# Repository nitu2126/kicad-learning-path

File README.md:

# KiCad Learning Path

> My hands-on journey from complete beginner to advanced electronics and PCB design with KiCad, built from small, simple circuits.
> Every project teaches one new idea and is documented with schematics, calculations, timing diagrams, layout rules, verification reports and manufacturing files.

## Table of contents

- [About this repository](#about-this-repository)
- [Learning approach](#learning-approach)
- [Projects so far](#projects-so-far)
- [Roadmap](#roadmap)
- [Coverage by track](#coverage-by-track)
- [Components index](#components-index)
- [What every project includes](#what-every-project-includes)
- [Repository structure](#repository-structure)
- [Tools](#tools)
- [How to open a project](#how-to-open-a-project)
- [Feedback](#feedback)
- [License](#license)

## About this repository

This repository documents my path through electronics and PCB design. I build one small circuit at a time, calculate it by hand, design it in KiCad, check it with ERC and DRC, prepare the manufacturing files, and write down what I learned.

The projects are ordered so that each one builds on the last. If you are learning too, start at Project 1 and work forward. The complete plan, with the components and ideas of every project, is in [ROADMAP.md](ROADMAP.md).

## Learning approach

| Rule | Why |
|---|---|
| One new idea per board | So you can see exactly what each component does |
| About 12 parts or fewer | Small enough to understand every connection |
| Through-hole parts and 0805 SMD only | Hand-solderable, no special equipment |
| 2-layer board, standard KiCad libraries | Cheap to build and easy to reproduce |
| Calculate first, then build, then measure | Theory is checked against reality |
| Timing or waveform diagram wherever signals change over time | Turns formulas into something you can verify on an oscilloscope |

## Projects so far

| # | Project | Preview | What it teaches | Documentation |
|---|---|---|---|---|
| 1 | [LED + Push-Button](01-led-button/) |  | Ohm's law, LED current limiting, resistors and switches, the full KiCad workflow, Gerber export | [README](01-led-button/README.md) · [Design notes](01-led-button/docs/DESIGN_NOTES.md) |
| 2 | [555 LED Blinker](02-555-blinker/) |  | Capacitors, RC time constant, the 555 timer, decoupling, ground pours and vias, timing diagram | [README](02-555-blinker/README.md) · [Design notes](02-555-blinker/docs/DESIGN_NOTES.md) |
| 3 | [Voltage Divider, Potentiometer and Light Sensor](03-voltage-divider/) |  | The voltage divider formula, the loading effect, potentiometer, LDR light sensor, test points, transfer curves | [README](03-voltage-divider/README.md) · [Design notes](03-voltage-divider/docs/DESIGN_NOTES.md) |
| 4 | [NPN Transistor Switch](04-npn-transistor-switch/) |  | The transistor as a switch, base resistor and saturation, flyback diode, net classes, switching waveform | [README](04-npn-transistor-switch/README.md) · [Design notes](04-npn-transistor-switch/docs/DESIGN_NOTES.md) |

## Roadmap

Fifteen simple circuits, from the first resistor to a complete microcontroller board.

| # | Project | Level | Track | Key ideas | Status |
|---|---|---|---|---|---|
| 1 | [LED + Push-Button](01-led-button/) | Beginner | Basics | Resistor, LED, switch, Ohm's law | Done |
| 2 | [555 LED Blinker](02-555-blinker/) | Beginner | Timing | Capacitor, timer IC, RC timing, decoupling | Done |
| 3 | [Voltage Divider, Potentiometer and Light Sensor](03-voltage-divider/) | Beginner | Analog | Divider formula, loading effect, LDR, test points | Done |
| 4 | [NPN Transistor Switch](04-npn-transistor-switch/) | Beginner | Analog and power | BJT, base resistor, flyback diode, saturation | In progress |
| 5 | Diode Power Entry and 5 V Linear Regulator | Beginner | Power | Reverse-polarity protection, regulator, heat dissipation | Planned |
| 6 | RC Low-Pass Filter | Intermediate | Analog | Cutoff frequency, step response, frequency response | Planned |
| 7 | Op-Amp Buffer and Amplifier | Intermediate | Analog | Feedback, gain, single-supply operation | Planned |
| 8 | Comparator Night-Light | Intermediate | Analog to digital | Comparator, hysteresis, sensor to switch | Planned |
| 9 | Logic Gates Trainer | Intermediate | Digital | 74HC gates, truth tables, logic levels, pull-downs | Planned |
| 10 | Switch Debouncer and D Flip-Flop | Intermediate | Digital | Contact bounce, SR latch, clocked memory | Planned |
| 11 | LED Chaser (555 + Decade Counter) | Advanced | Digital | Counters, clocking, sequential logic | Planned |
| 12 | MOSFET Load Switch and PWM Dimmer | Advanced | Power and analog | N-MOSFET, gate drive, PWM duty cycle | Planned |
| 13 | Buck Converter | Advanced | Power | Inductor, switching regulator, efficiency, loop layout | Planned |
| 14 | Digital Counter with 7-Segment Display | Advanced | Digital | Counter and decoder IC, display driving | Planned |
| 15 | Microcontroller Starter Board (ATtiny) | Advanced | Digital, analog and power | MCU, programming header, reset, ADC input | Planned |

**Status:** Done = built, verified and documented. In progress = designed or being documented. Planned = not started. The plan may be adjusted as I learn.

## Coverage by track

| Track | Projects |
|---|---|
| Analog | 3, 4, 6, 7, 8, 12, 15 |
| Digital | 2, 9, 10, 11, 14, 15 |
| Power | 4, 5, 12, 13, 15 |

## Components index

| Component | First used in |
|---|---|
| Resistor, LED, push-button | Project 1 |
| Capacitor (ceramic and electrolytic), 555 timer | Project 2 |
| Potentiometer, light-dependent resistor | Project 3 |
| NPN transistor | Project 4 |
| Diode, linear voltage regulator | Project 5 |
| Op-amp | Project 7 |
| Comparator | Project 8 |
| Logic gates | Project 9 |
| Flip-flop | Project 10 |
| Counter | Project 11 |
| MOSFET | Project 12 |
| Inductor, switching regulator | Project 13 |
| Decoder and 7-segment display | Project 14 |
| Microcontroller | Project 15 |

## What every project includes

- **README**: overview, specifications, images, bill of materials, netlist, testing and status
- **Design notes**: electronics theory, step-by-step calculations with worst-case analysis, KiCad configuration, layout rules and the reasons for them
- **Timing or waveform diagram** wherever signals change over time
- **Verification**: saved ERC and DRC reports and a Gerber viewer check
- **Manufacturing files**: Gerbers, drill files and BOM, ready for a low-cost fab
- **Test procedure**: expected measurements to compare against the real board

## Repository structure

```
kicad-learning-path/
├── README.md                    this index
├── ROADMAP.md                   the full 15-project plan
├── LICENSE
├── .gitignore
├── 01-led-button/
│   ├── README.md
│   ├── 01_led_button.kicad_pro / .kicad_sch / .kicad_pcb
│   ├── fabrication/             Gerbers, drill files, BOM
│   └── docs/                    design notes, schematic PDF, images, reports
├── 02-555-blinker/
│   ├── README.md
│   ├── 02_555_blinker.kicad_pro / .kicad_sch / .kicad_pcb
│   ├── fabrication/             Gerbers, drill files, BOM
│   └── docs/                    design notes, schematic PDF, timing diagram, images, reports
├── 03-voltage-divider/
│   ├── README.md
│   ├── 03_voltage_divider.kicad_pro / .kicad_sch / .kicad_pcb
│   ├── fabrication/             Gerbers, drill files, BOM
│   └── docs/                    design notes, schematic PDF, transfer curves, response diagram, images, reports
├── 04-npn-transistor-switch/
│   ├── README.md
│   ├── 04_npn_transistor_switch.kicad_pro / .kicad_sch / .kicad_pcb
│   ├── fabrication/             Gerbers, drill files, BOM
│   └── docs/                    design notes, schematic PDF, switching waveform, saturation curve, images, reports
└── 05-... to 15-...             added as each project is completed
```

**Naming:** project folders are `NN-short-name/` and the KiCad files inside are `NN_short_name.*`.

**Every project folder follows the same layout:**

```
NN-short-name/
├── README.md
├── NN_short_name.kicad_pro / .kicad_sch / .kicad_pcb
├── fabrication/
│   ├── gerbers/
│   ├── NN_short_name_gerbers.zip
│   └── bom.csv
└── docs/
    ├── DESIGN_NOTES.md
    ├── schematic.pdf
    ├── images/
    └── reports/
```

## Tools

| Tool | Version |
|---|---|
| KiCad | 10.x |
| Libraries | Standard KiCad libraries only |
| Target fab | Low-cost 2-layer service (for example JLCPCB) |
| Gerber check | KiCad Gerber Viewer or any third-party viewer |
| Version control | Git and GitHub |

## How to open a project

1. Install [KiCad](https://www.kicad.org/download/).
2. Clone or download this repository.
3. Open the `.kicad_pro` file inside any project folder.

## Feedback

Spotted a mistake in a calculation, or have a suggestion for a better layout or a simpler explanation? Please open an issue. Corrections are welcome.

## License

Released under the [MIT License](LICENSE).

Author: **Nitish Ghadage** · [GitHub](https://github.com/nitu2126)

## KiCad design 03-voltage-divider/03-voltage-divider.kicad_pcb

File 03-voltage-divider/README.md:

# Voltage Divider, Potentiometer and Light Sensor

> Three analog voltage dividers on one 5 V board: a fixed divider with a switchable load, a potentiometer, and a light-dependent resistor. Five test points make every voltage easy to measure.
> **Project 3** of my [KiCad learning path](../README.md): the voltage divider formula, the loading effect, the potentiometer and the LDR.

## Table of contents

- [Overview](#overview)
- [Key specifications](#key-specifications)
- [Gallery](#gallery)
- [Transfer curves and response](#transfer-curves-and-response)
- [How the circuits work](#how-the-circuits-work)
- [Design calculations (summary)](#design-calculations-summary)
- [Purpose of each component](#purpose-of-each-component)
- [Bill of materials](#bill-of-materials)
- [Netlist](#netlist)
- [Repository structure](#repository-structure)
- [Getting started](#getting-started)
- [Testing](#testing)
- [Verification status](#verification-status)
- [Future improvements](#future-improvements)
- [License](#license)

## Overview

Projects 1 and 2 produced outputs you could see: an LED that lit and an LED that blinked. This board produces **voltages you measure** with a multimeter. It teaches the most useful circuit in electronics, the voltage divider, in three forms:

| Section | Circuit | What it demonstrates |
|---|---|---|
| A | Fixed divider `R1` / `R2`, with a load `R3` switched in by jumper `JP1` | The divider formula, and how a load pulls the output down (the loading effect) |
| B | Potentiometer `RV1` across the supply | A variable divider, and how the wiper position sets the output |
| C | Light-dependent resistor `LDR1` and `R4` | Turning a changing resistance into a changing voltage |

New ideas compared with Project 2:

1. The voltage divider formula and its Thevenin equivalent
2. The loading effect, and why measuring a circuit can change it
3. A three-terminal potentiometer
4. A sensor whose resistance depends on light (power-law behaviour)
5. Test points for measurement
6. A jumper to change the circuit without soldering
7. Silkscreen graphics to group sections on the board

The full engineering write-up (theory, derivations, KiCad configuration, layout rules, test procedure) is in [`docs/DESIGN_NOTES.md`](docs/DESIGN_NOTES.md).

## Key specifications

| Parameter | Value |
|---|---|
| Supply voltage | 5 V DC via `J1` |
| Section A output `VA` (`TP3`) | 2.50 V unloaded, 1.67 V with `JP1` fitted |
| Section B output `VB` (`TP4`) | 0 V to 5 V, set by `RV1` |
| Section C output `VC` (`TP5`) | about 0.05 V in the dark, about 2 V at 10 lux, about 3.6 V at 100 lux (typical) |
| Supply current | about 0.95 mA typical, 1.29 mA maximum |
| Board layers | 2 |
| Board thickness | 1.6 mm |
| Copper weight | 1 oz (35 µm) |
| Board size | 70 × 40 mm |
| Components | 13 (8 circuit parts and 5 test points) |
| Pads / nets | 22 / 6 |
| Design tool | KiCad 10.0.x |
| ERC / DRC | 0 errors / 0 errors |

## Gallery

### Schematic

Full-size PDF: [`docs/schematic.pdf`](docs/schematic.pdf)

### PCB layout

### 3D views

| Top | Bottom |
|---|---|
|  |  |

## Transfer curves and response

### Transfer curves

| Plot | What it shows |
|---|---|
| A. Fixed divider | The output falls as the load resistance falls. With a 10 kΩ load (`JP1` fitted) it drops from 2.50 V to 1.67 V |
| B. Potentiometer | A straight line from 0 V to 5 V when unloaded. A 10 kΩ load on the wiper bends the curve (2.0 V instead of 2.5 V at mid-travel) |
| C. LDR divider | Output rises with light on a log scale. The shaded band is the part-to-part spread of the LDR (10 kΩ to 20 kΩ at 10 lux) |

### LDR response in time

When the light changes, the LDR follows with a lag of tens of milliseconds (datasheet: about 20 ms rising, 30 ms falling), so `VC` rises and falls smoothly rather than instantly. After bright light the real part can take seconds to settle back to its dark value. This diagram is an illustrative first-order approximation.

## How the circuits work

```
 +5V ──┬──────────────┬──────────────────┬──────────────┐
       R1 10k         │                  LDR1           │
       │              RV1 10k            │               │
 VA ───┼── JP1 ─ R3   │◄── wiper = VB    VC ──┬── TP5    │
       │         10k  │                       R4 10k     │
       R2 10k         │                       │          │
 GND ──┴──────────────┴───────────────────────┴──────────┘
```

**A. Fixed divider.** `R1` and `R2` form a series loop, so the same current flows through both. The output between them is the share of the supply that falls across `R2`. Fitting a shunt on `JP1` connects `R3` in parallel with `R2`, which lowers the lower half of the divider and pulls `VA` down.

**B. Potentiometer.** The two ends of `RV1` connect to `+5V` and `GND`. The wiper touches the track at an adjustable point and picks off the voltage there, so turning the shaft sweeps `VB` smoothly from 0 V to 5 V.

**C. LDR divider.** In the light the LDR's resistance is low, so most of the supply falls across `R4` and `VC` is high. In the dark the LDR's resistance is very high, so most of the supply falls across the LDR and `VC` is low.

## Design calculations (summary)

**Voltage divider:**

$$V_{out} = V_{in} \times \frac{R_2}{R_1 + R_2} \qquad V_A = 5.0\ \text{V} \times \frac{10\ \text{k}\Omega}{10\ \text{k}\Omega + 10\ \text{k}\Omega} = 2.50\ \text{V}$$

**Loading effect** (a load $R_L$ in parallel with $R_2$):

$$V_{A,loaded} = V_{in} \times \frac{R_2 \parallel R_L}{R_1 + (R_2 \parallel R_L)} = 5.0\ \text{V} \times \frac{5\ \text{k}\Omega}{10\ \text{k}\Omega + 5\ \text{k}\Omega} = 1.67\ \text{V}$$

**Potentiometer** (wiper at fraction $x$ of the travel, unloaded):

$$V_B = V_{in} \times x$$

**LDR divider** (LDR on the supply side):

$$V_C = V_{in} \times \frac{R_4}{R_4 + R_{LDR}} \qquad R_{LDR}(E) = R_{10}\left(\frac{E}{10\ \text{lux}}\right)^{-\gamma}$$

| Illuminance | `R_LDR` (typical: 15 kΩ at 10 lux, γ = 0.6) | `VC` |
|---|---|---|
| Dark (0 lux) | 1 MΩ or more | 0.05 V or less |
| 1 lux | 59.7 kΩ | 0.72 V |
| 10 lux | 15.0 kΩ | 2.00 V |
| 100 lux | 3.77 kΩ | 3.63 V |
| 1000 lux | 0.95 kΩ | 4.57 V |

The full derivations, tolerance analysis, loading tables and power checks are in [`docs/DESIGN_NOTES.md`](docs/DESIGN_NOTES.md#3-calculations).

## Purpose of each component

| Ref | Value | Purpose |
|---|---|---|
| `J1` | 2-pin header | Brings in 5 V (pin 1) and ground (pin 2) |
| `R1` | 10 kΩ | Upper resistor of the fixed divider |
| `R2` | 10 kΩ | Lower resistor of the fixed divider. Equal to `R1`, so `VA` is exactly half the supply |
| `R3` | 10 kΩ | Load resistor that `JP1` connects across `R2`, to demonstrate the loading effect |
| `JP1` | 2-pin header and shunt | Fitted: load connected. Removed: no load |
| `RV1` | 10 kΩ linear potentiometer | Variable divider. 10 kΩ draws only 0.5 mA and keeps the wiper impedance low |
| `LDR1` | GL5528 | Light sensor: 10 kΩ to 20 kΩ at 10 lux, at least 1 MΩ in the dark |
| `R4` | 10 kΩ | Fixed half of the LDR divider. Close to the LDR's resistance at typical room light, which gives good sensitivity |
| `TP1` | Test point | Probe point for `+5V` |
| `TP2` | Test point | Probe point for `GND` (reference for all measurements) |
| `TP3` | Test point | Probe point for `VA` |
| `TP4` | Test point | Probe point for `VB` |
| `TP5` | Test point | Probe point for `VC` |

## Bill of materials

| Ref | Qty | Value | Footprint | Description |
|---|---|---|---|---|
| `J1` | 1 | Conn_01x02_Pin | `PinHeader_1x02_P2.54mm_Vertical` | 2-pin header, 5 V in |
| `R1` | 1 | 10 kΩ | `R_0805_2012Metric` | Resistor, 1 % |
| `R2` | 1 | 10 kΩ | `R_0805_2012Metric` | Resistor, 1 % |
| `R3` | 1 | 10 kΩ | `R_0805_2012Metric` | Resistor, 1 % |
| `R4` | 1 | 10 kΩ | `R_0805_2012Metric` | Resistor, 1 % |
| `JP1` | 1 | Jumper_2_Open | `PinHeader_1x02_P2.54mm_Vertical` | 2-pin header, plus one 2.54 mm shunt |
| `RV1` | 1 | 10 kΩ | `Potentiometer_Bourns_3296W_Vertical` | Linear trimmer potentiometer |
| `LDR1` | 1 | GL5528 | `R_LDR_5.1x4.3mm_P3.4mm_Vertical` | CdS photoresistor, 5 mm |
| `TP1` to `TP5` | 5 | TestPoint | `TestPoint_THTPad_D2.0mm_Drill1.0mm` | Through-hole test points |

The same list is available as CSV in [`fabrication/bom.csv`](fabrication/bom.csv).

## Netlist

| Net | Connections |
|---|---|
| `+5V` | `J1`-1, `R1`-1, `RV1`-3, `LDR1`-1, `TP1` |
| `GND` | `J1`-2, `R2`-2, `R3`-2, `RV1`-1, `R4`-2, `TP2` |
| `VA` | `R1`-2, `R2`-1, `JP1`-1, `TP3` |
| `LOAD` | `JP1`-2, `R3`-1 |
| `VB` | `RV1`-2 (wiper), `TP4` |
| `VC` | `LDR1`-2, `R4`-1, `TP5` |

## Repository structure

This project lives in the `03-voltage-divider/` folder of the [kicad-learning-path](../README.md) repository.

```
03-voltage-divider/
├── README.md
├── 03_voltage_divider.kicad_pro     KiCad project file
├── 03_voltage_divider.kicad_sch     Schematic
├── 03_voltage_divider.kicad_pcb     PCB layout
├── fabrication/
│   ├── gerbers/                     Gerber and drill files
│   ├── 03_voltage_divider_gerbers.zip
│   └── bom.csv
└── docs/
    ├── DESIGN_NOTES.md              Full engineering documentation
    ├── schematic.pdf
    ├── images/                      Transfer curves, response diagram, screenshots, renders
    └── reports/                     ERC and DRC reports
```

## Getting started

### Open the project

1. Install [KiCad 10](https://www.kicad.org/download/).
2. Clone or download this repository.
3. Open `03-voltage-divider/03_voltage_divider.kicad_pro` in KiCad. The project uses only the standard KiCad libraries.

### Rebuild the manufacturing files

1. Open the PCB editor and run **Inspect → Design Rules Checker**. It should report 0 errors.
2. Open **File → Fabrication Outputs → Gerbers** and **Generate Drill Files**. The exact settings are listed in [`docs/DESIGN_NOTES.md`](docs/DESIGN_NOTES.md#9-manufacturing-outputs).
3. Zip the output folder.

### Order the PCB

Upload `fabrication/03_voltage_divider_gerbers.zip` to a PCB fabricator. Suggested options for a low-cost fab: 2 layers, 1.6 mm, 1 oz copper, HASL finish.

## Testing

Step-by-step measurements, expected values and a troubleshooting table are in [`docs/DESIGN_NOTES.md`](docs/DESIGN_NOTES.md#10-bring-up-and-testing). In short: apply 5 V, then use a multimeter on DC volts with the black probe on `TP2` and the red probe on `TP3`, `TP4` and `TP5`. You should read about 2.5 V (1.67 V with `JP1` fitted), a sweep from 0 V to 5 V as you turn `RV1`, and a voltage that follows the light on `LDR1`.

## Verification status

| Check | Result |
|---|---|
| Electrical Rules Check (ERC) | 0 errors |
| Design Rules Check (DRC) | 0 errors, 0 unrouted nets |
| Gerber viewer check | Passed |
| Physical board built and tested | Not yet |

Reports: [`docs/reports/`](docs/reports/)

## Future improvements

- Buffer the divider outputs with an op-amp (Project 7) so loading no longer matters
- Compare `VC` with the potentiometer voltage `VB` using a comparator (Project 8) to build a night-light with an adjustable threshold
- Add mounting holes
- Try a different LDR value and note how `R4` should change

## License

Released under the [MIT License](../LICENSE).

Author: **Nitish Ghadage** · [GitHub](https://github.com/nitu2126)

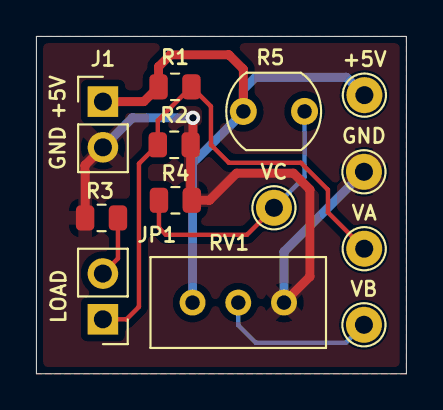
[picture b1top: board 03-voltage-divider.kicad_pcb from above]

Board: 2 copper layers, 20.6 x 18.7 mm, 13 parts (0 on the bottom side), 6 nets.

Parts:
+5V: +5V; TestPoint_THTPad_D2.0mm_Drill1.0mm
GND: GND; TestPoint_THTPad_D2.0mm_Drill1.0mm
J1: POWER; PinHeader_1x02_P2.54mm_Vertical
JP1: Jumper_2_Open; PinHeader_1x02_P2.54mm_Vertical
R1, R2, R3, R4: 10k; R_0805_2012Metric
R5: GL5528; R_LDR_5.1x4.3mm_P3.4mm_Vertical
RV1: 10k; Potentiometer_Bourns_3296W_Vertical
VA: VA; TestPoint_THTPad_D2.0mm_Drill1.0mm
VB: VB; TestPoint_THTPad_D2.0mm_Drill1.0mm
VC: VC; TestPoint_THTPad_D2.0mm_Drill1.0mm

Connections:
+5V: +5V.1 (1_1), J1.1, R1.1, R5.1, RV1.1
GND: GND.1 (1_1), J1.2, R2.2, R3.2, R4.2, RV1.3
unnamed: JP1.1 (A), R1.2, R2.1, VA.1 (1_1)
unnamed: JP1.2 (B), R3.1
unnamed: R4.1, R5.2, VC.1 (1_1)
unnamed: RV1.2, VB.1 (1_1)

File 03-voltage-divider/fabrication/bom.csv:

"Id";"Designator";"Footprint";"Quantity";"Designation";"Supplier and ref";
1;"+5V";"TestPoint_THTPad_D2.0mm_Drill1.0mm";1;"+5V";;;
2;"GND";"TestPoint_THTPad_D2.0mm_Drill1.0mm";1;"GND";;;
3;"J1";"PinHeader_1x02_P2.54mm_Vertical";1;"POWER";;;
4;"JP1";"PinHeader_1x02_P2.54mm_Vertical";1;"Jumper_2_Open";;;
5;"R1, R2, R3, R4";"R_0805_2012Metric";4;"10k";;;
6;"R5";"R_LDR_5.1x4.3mm_P3.4mm_Vertical";1;"GL5528";;;
7;"RV1";"Potentiometer_Bourns_3296W_Vertical";1;"10k";;;
8;"VA";"TestPoint_THTPad_D2.0mm_Drill1.0mm";1;"VA";;;
9;"VB";"TestPoint_THTPad_D2.0mm_Drill1.0mm";1;"VB";;;
10;"VC";"TestPoint_THTPad_D2.0mm_Drill1.0mm";1;"VC";;;

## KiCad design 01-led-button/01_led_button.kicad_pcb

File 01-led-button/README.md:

# LED + Push-Button PCB

> A fully documented KiCad 10 project: a 5 V push-button that lights a red LED through a current-limiting resistor.
> **Project 1** of my KiCad learning path, from basic electronics to advanced PCB design.

[← Back to all projects](../README.md)

## Table of contents

- [Overview](#overview)
- [Key specifications](#key-specifications)
- [Gallery](#gallery)
- [How the circuit works](#how-the-circuit-works)
- [Design calculations (summary)](#design-calculations-summary)
- [Bill of materials](#bill-of-materials)
- [Netlist](#netlist)
- [Repository structure](#repository-structure)
- [Getting started](#getting-started)
- [Testing](#testing)
- [Verification status](#verification-status)
- [Future improvements](#future-improvements)
- [Learning-path roadmap](#learning-path-roadmap)
- [License](#license)

## Overview

This board is deliberately simple so that the **complete professional PCB workflow** is covered end to end:

1. Electronics fundamentals and component calculation
2. Schematic capture with power flags and a clean ERC
3. Footprint assignment
4. Board setup: stackup, design constraints, net classes
5. Placement, routing and copper pour
6. DRC, 3D check and Gerber verification
7. Manufacturing file export for a low-cost 2-layer fab

**What it does:** a 5 V supply is connected to header `J1`. While push-button `SW1` is held down, current flows through resistor `R1` and LED `D1`, and the LED lights. `R1` limits the current to about 9 mA.

The full engineering write-up (theory, derivations, KiCad configuration, layout rules, manufacturing settings) is in [`docs/DESIGN_NOTES.md`](docs/DESIGN_NOTES.md).

## Key specifications

| Parameter                 | Value                              |
| ------------------------- | ---------------------------------- |
| Supply voltage            | 5 V DC (via `J1`)                  |
| LED current (nominal)     | ≈ 9.1 mA                           |
| Current-limit resistor    | 330 Ω, 0805, 1 %                   |
| LED                       | Red, 0805, forward voltage ≈ 2.0 V |
| Board layers              | 2                                  |
| Board thickness           | 1.6 mm                             |
| Copper weight             | 1 oz (35 µm)                       |
| Board size                | 18.750 × 11.480 mm                 |
| Components                | 4 (`J1`, `SW1`, `R1`, `D1`)        |
| Pads / nets / vias        | 10 / 4 / 0                         |
| Minimum track / clearance | 0.2 mm / 0.2 mm                    |
| Design tool               | KiCad 10.0.x                       |
| ERC / DRC                 | 0 errors / 0 errors                |

## Gallery

### Schematic

Full-size PDF: [`docs/schematic.pdf`](docs/schematic.pdf)

### PCB layout

### 3D views

| Top                                   | Bottom                                      |
| ------------------------------------- | ------------------------------------------- |
|  |  |

## How the circuit works

```
+5V ──► SW1 (push button) ──► R1 (330 Ω) ──► D1 (red LED) ──► GND
```

- `J1` brings in 5 V on pin 1 and ground on pin 2.
- `SW1` is normally open. Pressing it completes the loop.
- `R1` drops the surplus voltage so the LED current is safe.
- `D1` conducts only in the direction of the triangle (anode to cathode) and lights up.
- The same current flows through every part, because they are in series.

## Design calculations (summary)

**Ohm's law:**

$$V = I \times R$$

**Resistor value for a target LED current:**

$$R = \frac{V_S - V_F}{I_F} = \frac{5.0\ \text{V} - 2.0\ \text{V}}{10\ \text{mA}} = 300\ \Omega \;\rightarrow\; \text{330}\ \Omega\ \text{(standard E12 value)}$$

**Actual current with the standard value:**

$$I = \frac{V_S - V_F}{R} = \frac{3.0\ \text{V}}{330\ \Omega} \approx 9.09\ \text{mA}$$

**Power:**

$$P = V \times I = I^2 R$$

| Element           | Voltage drop | Current | Power                                  |
| ----------------- | ------------ | ------- | -------------------------------------- |
| `R1` (330 Ω)      | 3.0 V        | 9.09 mA | 27.3 mW (rating of 0805: about 125 mW) |
| `D1` (red LED)    | ≈ 2.0 V      | 9.09 mA | 18.2 mW                                |
| `SW1` (closed)    | ≈ 0 V        | 9.09 mA | ≈ 0 mW                                 |
| Total from supply | 5.0 V        | 9.09 mA | 45.5 mW                                |

Worst-case analysis (supply ±5 %, resistor ±1 %, LED forward voltage 1.8 V to 2.2 V) gives a current between **7.65 mA and 10.56 mA**, which is safe for the LED and the resistor. The full derivation is in [`docs/DESIGN_NOTES.md`](docs/DESIGN_NOTES.md#3-calculations).

## Bill of materials

| Ref   | Qty | Value          | Footprint                         | Description                   |
| ----- | --- | -------------- | --------------------------------- | ----------------------------- |
| `J1`  | 1   | Conn_01x02_Pin | `PinHeader_1x02_P2.54mm_Vertical` | 2-pin 2.54 mm header (5 V in) |
| `SW1` | 1   | SW_Push        | `SW_PUSH_6mm`                     | 6 mm tactile push-button      |
| `R1`  | 1   | 330 Ω          | `R_0805_2012Metric`               | Resistor, 1 %, 1/8 W          |
| `D1`  | 1   | RED            | `LED_0805_2012Metric`             | Red LED, 0805                 |

The same list is available as CSV in [`fabrication/bom.csv`](fabrication/bom.csv).

## Netlist

| Net             | Connections              |
| --------------- | ------------------------ |
| `+5V`           | `J1` pin 1, `SW1` pin 1  |
| `Net-(R1-Pad1)` | `SW1` pin 2, `R1` pin 1  |
| `Net-(D1-A)`    | `R1` pin 2, `D1` anode   |
| `GND`           | `D1` cathode, `J1` pin 2 |

## Repository structure

```
kicad-learning-path/
├── README.md                    Index of all projects
├── LICENSE
├── .gitignore
└── 01-led-button/               This project
    ├── README.md                You are here
    ├── 01_led_button.kicad_pro  KiCad project file
    ├── 01_led_button.kicad_sch  Schematic
    ├── 01_led_button.kicad_pcb  PCB layout
    ├── fabrication/
    │   ├── gerbers/             Gerber and drill files
    │   ├── 01_led_button_gerbers.zip
    │   └── bom.csv
    └── docs/
        ├── DESIGN_NOTES.md      Full engineering documentation
        ├── schematic.pdf
        ├── images/              Screenshots and 3D renders
        └── reports/             ERC and DRC reports
```

## Getting started

### Open the project

1. Install [KiCad 10](https://www.kicad.org/download/).
2. Clone or download the `kicad-learning-path` repository.
3. Open `01-led-button/01_led_button.kicad_pro` in KiCad. The project uses only the standard KiCad libraries.

### Rebuild the manufacturing files

1. Open the PCB editor and run **Inspect → Design Rules Checker**. It should report 0 errors.
2. Open **File → Fabrication Outputs → Gerbers** and **Generate Drill Files**. The exact settings are listed in [`docs/DESIGN_NOTES.md`](docs/DESIGN_NOTES.md#8-manufacturing-outputs).
3. Zip the output folder.

### Order the PCB

Upload `fabrication/01_led_button_gerbers.zip` to a PCB fabricator. Suggested options for a low-cost fab: 2 layers, 1.6 mm, 1 oz copper, HASL finish.

## Testing

Bring-up procedure and expected measurements are in [`docs/DESIGN_NOTES.md`](docs/DESIGN_NOTES.md#9-bring-up-and-testing). In short: apply 5 V, press `SW1`, and the LED lights; the voltage across `R1` should read about 3.0 V.

## Verification status

| Check                           | Result                    |
| ------------------------------- | ------------------------- |
| Electrical Rules Check (ERC)    | 0 errors                  |
| Design Rules Check (DRC)        | 0 errors, 0 unrouted nets |
| Gerber viewer check             | Passed                    |
| Physical board built and tested | Not yet                   |

Reports: [`docs/reports/`](docs/reports/)

## Future improvements

- Add reverse-polarity protection on `J1`
- Add mounting holes
- Reduce silkscreen text size and keep it clear of the board edge
- Add a second LED as a power indicator
- Replace the header with a USB-C connector (see Project 4)

## Learning-path roadmap

| #   | Project                    | Status  |
| --- | -------------------------- | ------- |
| 1   | Push-button LED board      | Done    |
| 2   | 555 timer LED blinker      | Planned |
| 3   | Transistor/MOSFET driver   | Planned |
| 4   | USB-C to 3.3 V power board | Planned |
| 5   | Microcontroller board      | Planned |
| 6   | Advanced capstone          | Planned |

## License

Released under the [MIT License](../LICENSE). Replace with a hardware license such as CERN-OHL-P-2.0 if you prefer.

Author: **Nitish Ghadage** · [GitHub](https://github.com/nitu2126)

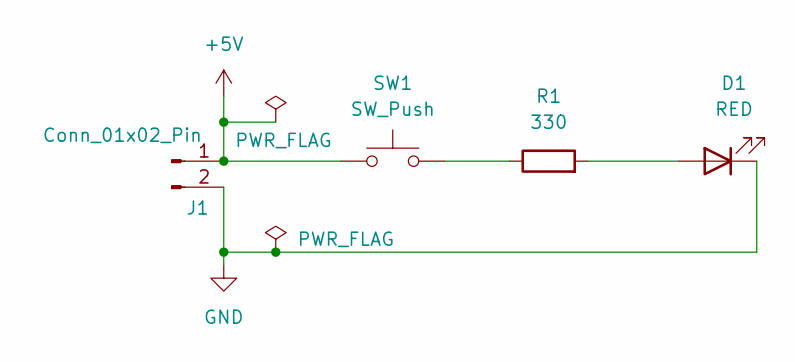
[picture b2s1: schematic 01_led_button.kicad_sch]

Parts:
D1: RED; LED_0805_2012Metric
J1: Conn_01x02_Pin; PinHeader_1x02_P2.54mm_Vertical
R1: 330; R_0805_2012Metric
SW1: SW_Push; SW_PUSH_6mm

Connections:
+5V: J1.1, SW1.1
GND: D1.1 (K), J1.2
unnamed: D1.2 (A), R1.2
unnamed: R1.1, SW1.2

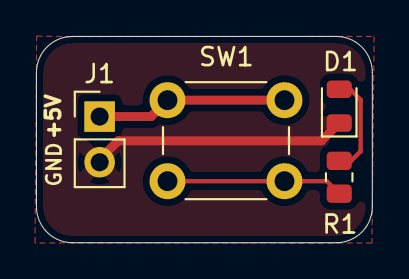
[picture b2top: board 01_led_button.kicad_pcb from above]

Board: 2 copper layers, 18.7 x 11.5 mm, 4 parts (0 on the bottom side), 4 nets.

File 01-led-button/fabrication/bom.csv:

"Id";"Designator";"Footprint";"Quantity";"Designation";"Supplier and ref";
1;"D1";"LED_0805_2012Metric";1;"RED";;;
2;"J1";"PinHeader_1x02_P2.54mm_Vertical";1;"Conn_01x02_Pin";;;
3;"R1";"R_0805_2012Metric";1;"330";;;
4;"SW1";"SW_PUSH_6mm";1;"SW_Push";;;

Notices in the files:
01-led-button/README.md:
License: MIT
03-voltage-divider/03-voltage-divider.kicad_pcb:
©NITISH GHADAGE
